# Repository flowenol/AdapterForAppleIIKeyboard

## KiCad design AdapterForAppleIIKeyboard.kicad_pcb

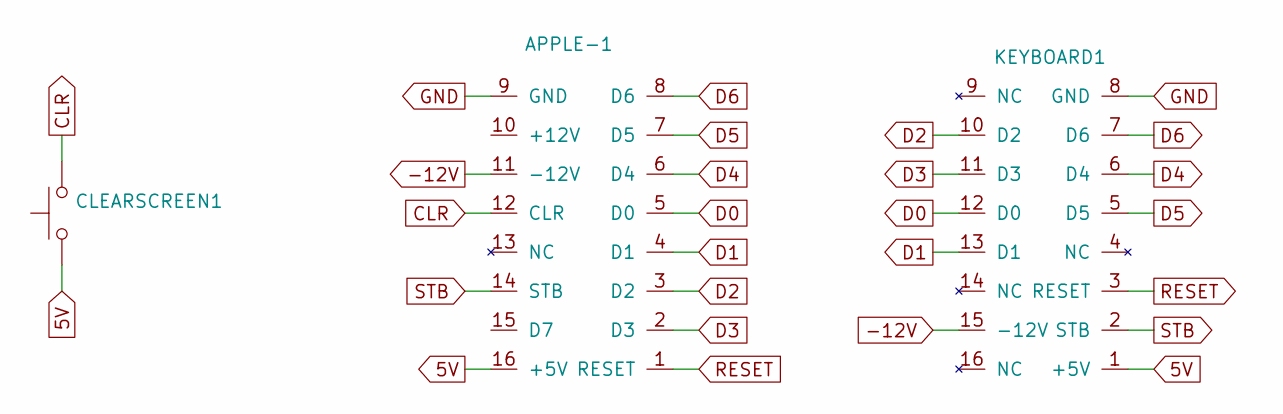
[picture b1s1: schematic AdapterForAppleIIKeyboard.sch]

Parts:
APPLE-1: APPLE-1; DIP-16_W7.62mm_LongPads
CLEARSCREEN1: CLEAR SCREEN; SW_PUSH_6mm
KEYBOARD1: KEYBOARD; DIP-16_W7.62mm_LongPads

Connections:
5V: APPLE-1.16 (+5V), CLEARSCREEN1.1, KEYBOARD1.1 (+5V)
-12V: APPLE-1.11 (-12V), KEYBOARD1.15 (-12V)
CLR: APPLE-1.12 (CLR), CLEARSCREEN1.2
D0: APPLE-1.5 (D0), KEYBOARD1.12 (D0)
D1: APPLE-1.4 (D1), KEYBOARD1.13 (D1)
D2: APPLE-1.3 (D2), KEYBOARD1.10 (D2)
D3: APPLE-1.2 (D3), KEYBOARD1.11 (D3)
D4: APPLE-1.6 (D4), KEYBOARD1.6 (D4)
D5: APPLE-1.7 (D5), KEYBOARD1.5 (D5)
D6: APPLE-1.8 (D6), KEYBOARD1.7 (D6)
GND: APPLE-1.9 (GND), KEYBOARD1.8 (GND)
RESET: APPLE-1.1 (RESET), KEYBOARD1.3 (RESET)
STB: APPLE-1.14 (STB), KEYBOARD1.2 (STB)

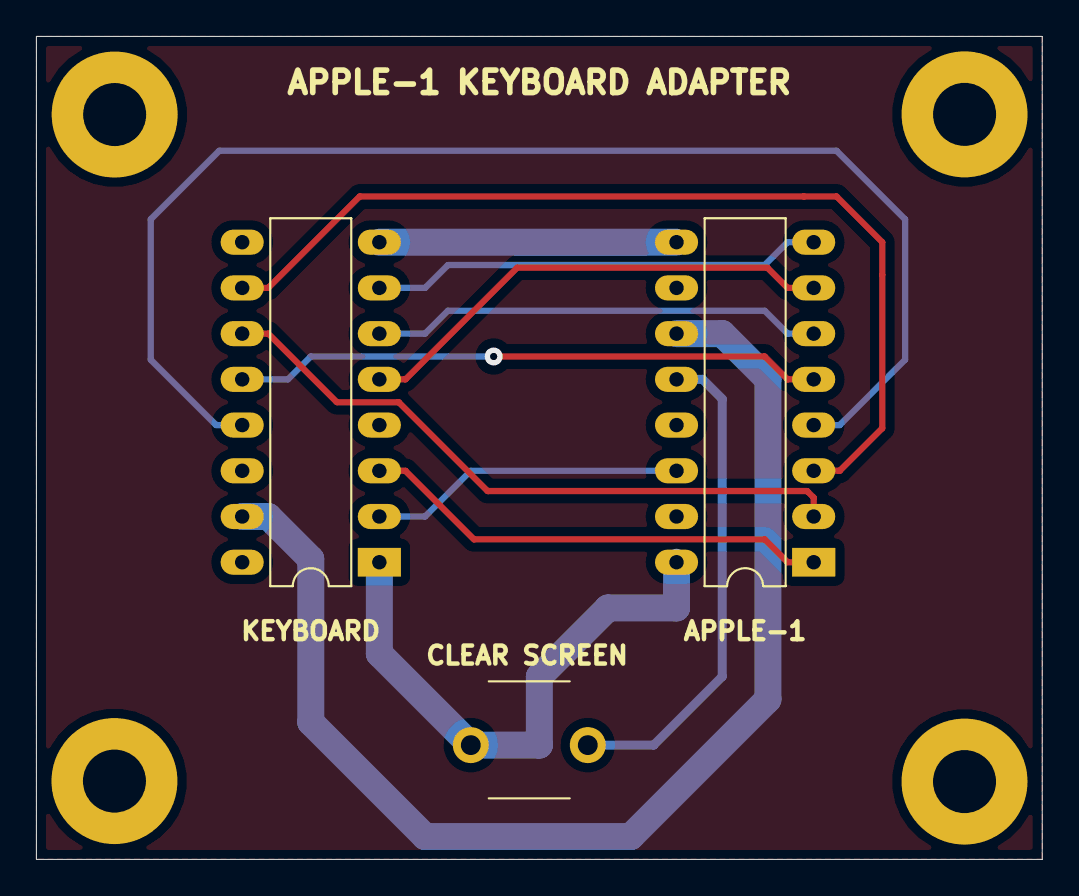
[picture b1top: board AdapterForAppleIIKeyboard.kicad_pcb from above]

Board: 2 copper layers, 55.9 x 45.7 mm, 3 parts (0 on the bottom side), 13 nets.

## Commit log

2021-03-15 added mounting holes
